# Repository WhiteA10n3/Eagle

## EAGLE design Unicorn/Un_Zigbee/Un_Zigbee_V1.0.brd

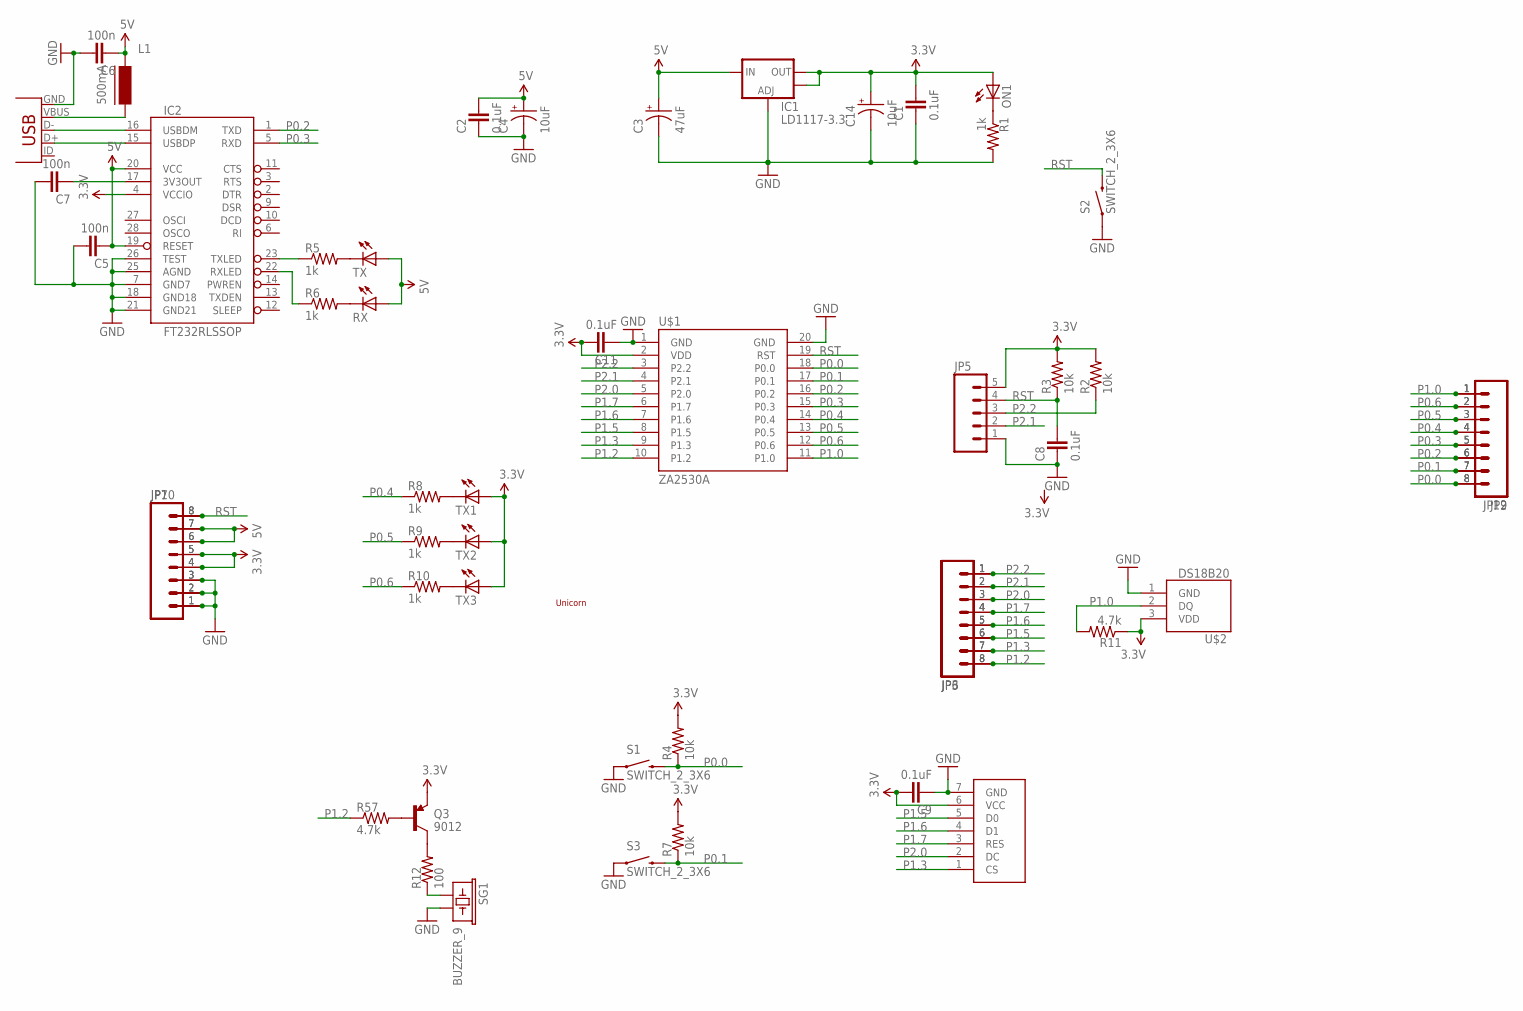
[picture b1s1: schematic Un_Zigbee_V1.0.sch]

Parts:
C1, C2, C8, C9, C11: 0.1uF; 0603-CAP
C3: 47uF; EIA3216
C4, C14: 10uF; EIA3216
C5, C6, C7: 100n; 0603-CAP
IC1: LD1117-3.3; SOT223
IC2: FT232RLSSOP; SSOP28DB
JP3, JP6, JP7, JP9, JP10, JP12: M08; 1X08
JP5: M05PTH; 1X05
L1: 500mA; FB805
ON1: LED0603; LED-0603
Q3: 9012; SOT23-3
R1, R5, R6, R8, R9, R10: 1k; 0603-RES
R2, R3, R4, R7: 10k; 0603-RES
R11, R57: 4.7k; 0603-RES
R12: 100; 0603-RES
RX: LED0603; LED-0603
S1, S2, S3: SWITCH_2_3X6; TACTILE-SWITCH-1101NE
SG1: BUZZER_9; BUZZER-9MM
TX, TX1, TX2, TX3: LED0603; LED-0603
U$1: ZA2530A
U$2: DS18B20; TO-92
U$3: UNICORN_1
U$7: OLED_2
U$10: USB_5-SMD; USB-MINIB

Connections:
3.3V: C1.1, C9.1, C11.1, C14.A (+), IC1.2 (OUT), IC1.4 (OUT), IC2.4 (VCCIO), JP5.5, JP7.4, JP7.5, JP10.4, JP10.5, ON1.A, Q3.2 (E), R2.2, R3.2, R4.2, R7.2, R11.1, TX1.A, TX2.A, TX3.A, U$1.2 (VDD), U$2.3 (VDD), U$7.6 (VCC)
5V: C2.1, C3.A (+), C4.A (+), C5.2, C6.2, IC1.3 (IN), IC2.19 (RESET), IC2.20 (VCC), JP7.6, JP7.7, JP10.6, JP10.7, L1.1, RX.A, TX.A
GND: C1.2, C2.2, C3.C (-), C4.C (-), C5.1, C6.1, C7.1, C8.2, C9.2, C11.2, C14.C (-), IC1.1 (ADJ), IC2.7 (GND7), IC2.18 (GND18), IC2.21 (GND21), IC2.25 (AGND), IC2.26 (TEST), JP5.1, JP7.1, JP7.2, JP7.3, JP10.1, JP10.2, JP10.3, R1.2, S1.P$1 (1), S2.P$1 (1), S3.P$1 (1), SG1.- (2), U$1.1 (GND), U$1.20 (GND), U$2.1 (GND), U$7.7 (GND), U$10.GND
unnamed: ON1.C, R1.1
unnamed: Q3.3 (C), R12.2
unnamed: L1.2, U$10.VBUS
unnamed: R8.2, TX1.C
unnamed: IC2.16 (USBDM), U$10.D-
unnamed: IC2.15 (USBDP), U$10.D+
unnamed: IC2.23 (TXLED), R5.1
unnamed: R5.2, TX.C
unnamed: R6.2, RX.C
unnamed: IC2.22 (RXLED), R6.1
unnamed: R9.2, TX2.C
unnamed: R10.2, TX3.C
unnamed: C7.2, IC2.17 (3V3OUT)
unnamed: Q3.1 (B), R57.2
unnamed: R12.1, SG1.+ (1)
P0.0: JP9.8, JP12.8, R4.1, S1.P$2 (2), U$1.18 (P0.0)
P0.1: JP9.7, JP12.7, R7.1, S3.P$2 (2), U$1.17 (P0.1)
P0.2: IC2.1 (TXD), JP9.6, JP12.6, U$1.16 (P0.2)
P0.3: IC2.5 (RXD), JP9.5, JP12.5, U$1.15 (P0.3)
P0.4: JP9.4, JP12.4, R8.1, U$1.14 (P0.4)
P0.5: JP9.3, JP12.3, R9.1, U$1.13 (P0.5)
P0.6: JP9.2, JP12.2, R10.1, U$1.12 (P0.6)
P1.0: JP9.1, JP12.1, R11.2, U$1.11 (P1.0), U$2.2 (DQ)
P1.2: JP3.8, JP6.8, R57.1, U$1.10 (P1.2)
P1.3: JP3.7, JP6.7, U$1.9 (P1.3), U$7.1 (CS)
P1.5: JP3.6, JP6.6, U$1.8 (P1.5), U$7.5 (D0)
P1.6: JP3.5, JP6.5, U$1.7 (P1.6), U$7.4 (D1)
P1.7: JP3.4, JP6.4, U$1.6 (P1.7), U$7.3 (RES)
P2.0: JP3.3, JP6.3, U$1.5 (P2.0), U$7.2 (DC)
P2.1: JP3.2, JP5.2, JP6.2, U$1.4 (P2.1)
P2.2: JP3.1, JP5.3, JP6.1, R2.1, U$1.3 (P2.2)
RST: C8.1, JP5.4, JP7.8, JP10.8, R3.1, S2.P$2 (2), U$1.19 (RST)

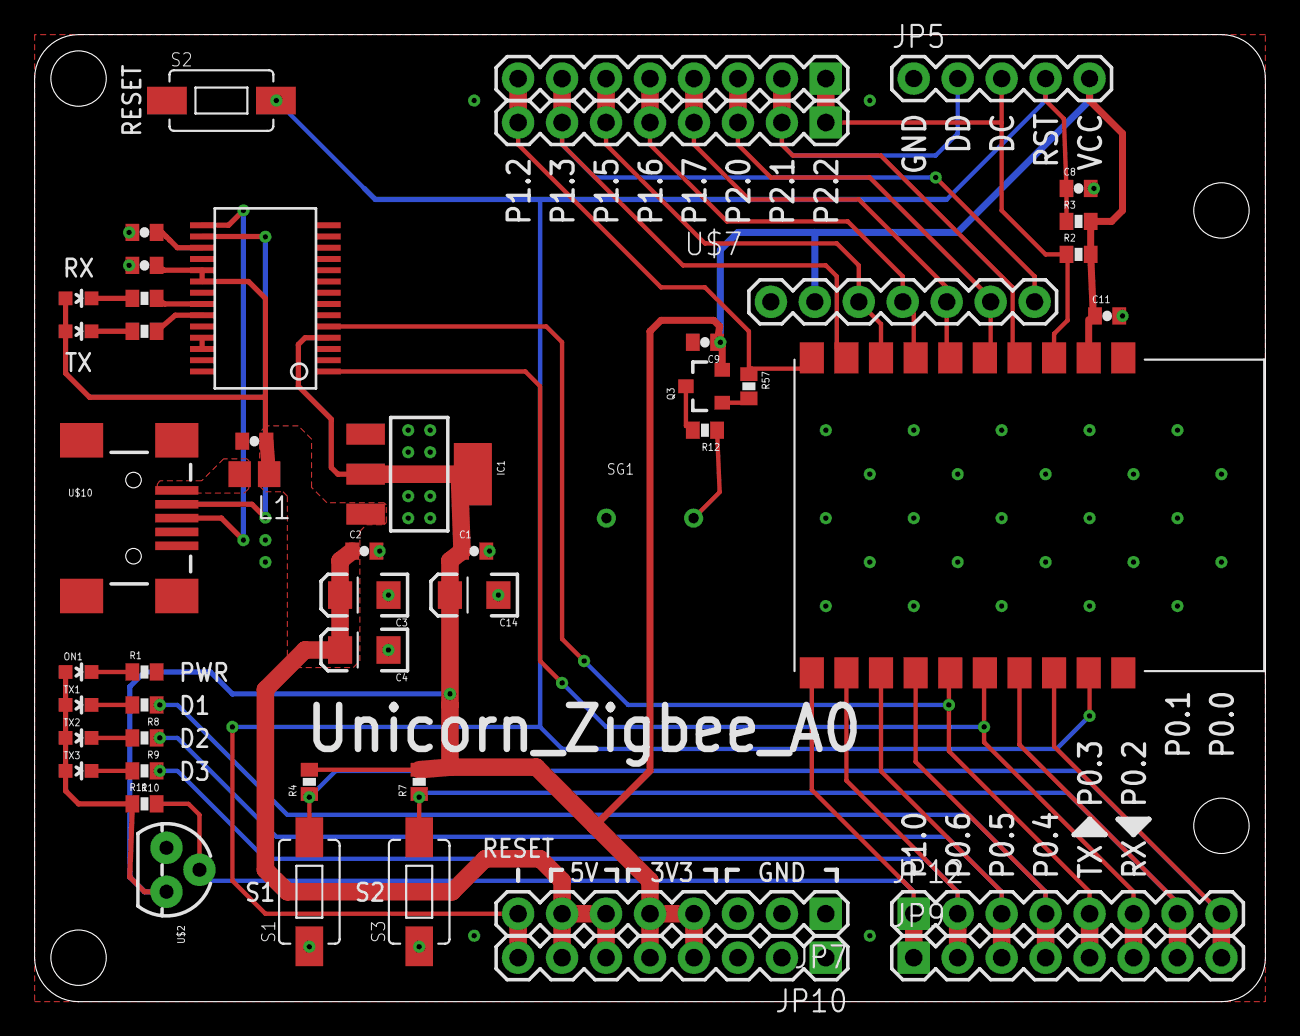
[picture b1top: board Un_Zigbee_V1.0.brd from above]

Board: 2 copper layers, 71.1 x 55.9 mm, 50 parts (0 on the bottom side), 35 nets.

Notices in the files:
parts and their libraries:
1SparkFun: Licensing: CC v3.0 Share-Alike You are welcome to use this library for commercial purposes.
